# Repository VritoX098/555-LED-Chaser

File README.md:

# LED Chaser (Blinky Board)

A 10-LED chaser board built with a 555 timer and CD4017 counter. My first PCB design, made through Hack Club's Forge program.

---

---

---

---

## What it does

10 LEDs light up in sequence, one after another, creating a chasing effect. There's a potentiometer (RV1) that lets you adjust the speed of the chase, turn it one way and it goes fast, the other way and it slows down.

## How to use

1. Power it with 5V via the J1 header (2-pin socket)
2. The LEDs (D1-D10) will start chasing in sequence
3. Twist RV1 to change the blink speed

Pretty simple honestly. Plug it in and watch it go.

## Why I made this

Wanted to get into hardware and PCB design. This was the perfect beginner project to learn KiCad, understand how oscillators and counters work, and actually ship something physical. Also the batman shaped board just looks cool lol.

## What I learned

- How a 555 timer works (astable mode generates a clock pulse)
- How a CD4017 decade counter distributes that pulse across 10 outputs
- Difference between SMD and THT components
- What global labels are and why power flags exist
- How to import custom footprints (CD4017 wasn't in KiCad by default)
- PCB routing is harder than it looks (redid mine twice)

---

# Bill of Materials (BOM)

**Project:** LED Chaser (Blinky Board)  
**Total Components:** 19  
**Estimated Total Cost:** $5.09 + 33 + 7 = 45$ (Including shipping and PCB)

| Ref | Qty | Value | Footprint | Links | Unit Price | Total |
|-----|-----|-------|-----------|-------|------------|-------|
| C1 | 1 | 1 µF | Capacitor_THT:CP_Radial_D5.0mm_P2.00mm | [LCSC C43342](https://www.lcsc.com/product-detail/C43342.html) / [LCSC C1579562](https://www.lcsc.com/product-detail/C1579562.html) | $0.14 | $0.14 |
| C2 | 1 | 0.01 µF | Capacitor_THT:C_Disc_D7.5mm_W2.5mm_P5.00mm | [LCSC C454399](https://www.lcsc.com/product-detail/C454399.html) | $0.17 | $0.17 |
| D1-D10 | 10 | LED | LED_THT:LED_D3.0mm | [LCSC C264302](https://www.lcsc.com/product-detail/C264302.html) / [LCSC C99771](https://www.lcsc.com/product-detail/C99771.html) | $0.10 | $1.00 |
| J1 | 1 | Conn_01x02_Socket | PinHeader_1x02_P2.54mm_Vertical | [DigiKey 929500-01-02-RK](https://www.digikey.com/en/products/result?keywords=929500-01-02-RK) | $0.10 | $0.10 |
| J2 | 1 | Conn_01x01_Socket | PinHeader_1x01_P2.54mm_Vertical | [DigiKey PRPC001DAAN-RC](https://www.digikey.com/en/products/result?keywords=PRPC001DAAN-RC) | $0.05 | $0.05 |
| R1 | 1 | 1kΩ | R_Axial_DIN0207_L6.3mm_D2.5mm_P7.62mm_Horizontal | [DigiKey CFR-25JR-52-1K](https://www.digikey.com/en/products/detail/yageo/CFR-25JR-52-1K/11974) | $0.05 | $0.05 |
| R2 | 1 | 470Ω | R_Axial_DIN0207_L6.3mm_D2.5mm_P7.62mm_Horizontal | [DigiKey CFR-25JR-52-470R](https://www.digikey.com/en/products/detail/yageo/CFR-25JR-52-470R/11966) | $0.05 | $0.05 |
| RV1 | 1 | 50kΩ | Potentiometer_Vishay_T93YA_Vertical | [LCSC C7061697](https://www.lcsc.com/product-detail/Trimmer-Potentiometers_VISHAY-T93YA503KT20_C7061697.html) / [DigiKey 3296W-1-503LF](https://www.digikey.co.uk/en/products/detail/bourns-inc/3296W-1-503LF/1088059) | $1.58 | $1.58 |
| U1 | 1 | NE555P | DIP-8_W7.62mm | [LCSC C46749](https://www.lcsc.com/product-detail/Timers-Clocks_NE555P_C46749.html) | $0.56 | $0.56 |
| U2 | 1 | CD4017BE | N16 (DIP-16) | [LCSC C34519](https://www.lcsc.com/product-detail/Counters-Dividers_TI-CD4017BE_C34519.html) | $1.39 | $1.39 |

---

---

## Cost Breakdown

| Part | Cost |
|------|------|
| Capacitors (C1, C2) | $0.31 |
| LEDs (x10) | ~$1.00 |
| Resistors (R1, R2) | $0.10 |
| Potentiometer (RV1) | $1.58 |
| NE555P (U1) | $0.56 |
| CD4017BE (U2) | $1.39 |
| Pin Headers (J1, J2) | $0.15 |
| **PCB (JLCPCB)** | ~$2.00 (for 5 boards) |
| **Total** | **~$7.34** |

> Note: The PCB cost isn't in the component BOM above because it's separate. Total project cost ends up around $7-10 depending on shipping and where you buy. Hack Club Forge covers this, so it's basically free for me lol.

---

## Credits

Built through [Hack Club's Forge](https://forge.hackclub.com) program.

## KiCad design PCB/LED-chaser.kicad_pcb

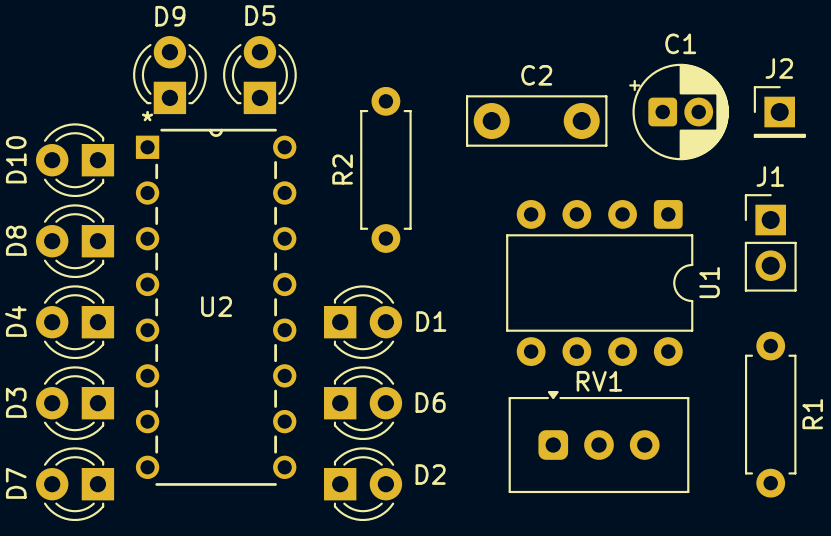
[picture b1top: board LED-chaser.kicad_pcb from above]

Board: 2 copper layers, 19 parts (0 on the bottom side), 18 nets, no tracks yet.

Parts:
C1: 1 uF; CP_Radial_D5.0mm_P2.00mm
C2: 0.01 uF; C_Disc_D7.5mm_W2.5mm_P5.00mm
D1, D2, D3, D4, D5, D6, D7, D8, D9, D10: LED; LED_D3.0mm
J1: Conn_01x02_Socket; PinHeader_1x02_P2.54mm_Vertical
J2: Conn_01x01_Socket; PinHeader_1x01_P2.54mm_Vertical
R1: 1k; R_Axial_DIN0207_L6.3mm_D2.5mm_P7.62mm_Horizontal
R2: 470; R_Axial_DIN0207_L6.3mm_D2.5mm_P7.62mm_Horizontal
RV1: 50k; Potentiometer_Vishay_T93YA_Vertical
U1: NE555P; DIP-8_W7.62mm
U2: 4017; N16

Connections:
+5V: J1.1, R1.1, U1.4 (~RST), U1.8 (VCC), U2.16 (VDD)
GND: C1.2, C2.2, J1.2, R2.2, U1.1 (GND), U2.8 (VSS), U2.13 (CKEN), U2.15 (Reset)
unnamed: D1.2 (A), U2.11 (Q9)
unnamed: D1.1 (K), D2.1 (K), D3.1 (K), D4.1 (K), D5.1 (K), D6.1 (K), D7.1 (K), D8.1 (K), D9.1 (K), D10.1 (K), R2.1
unnamed: D2.2 (A), U2.9 (Q8)
unnamed: D3.2 (A), U2.6 (Q7)
unnamed: D4.2 (A), U2.5 (Q6)
unnamed: D5.2 (A), U2.1 (Q5)
unnamed: D6.2 (A), U2.10 (Q4)
unnamed: D7.2 (A), U2.7 (Q3)
unnamed: D8.2 (A), U2.4 (Q2)
unnamed: D9.2 (A), U2.2 (Q1)
unnamed: D10.2 (A), U2.3 (Q0)
unnamed: R1.2, RV1.1
unnamed: C2.1, U1.5 (CONT)
unnamed: RV1.2, U1.7 (DISCH)
unnamed: C1.1, RV1.3, U1.2 (TRIG), U1.6 (THRES)
OUT: J2.1 (Pin_1_1), U1.3 (OUT), U2.14 (CLK)

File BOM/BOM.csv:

"Reference","Qty","Value","DNP","Exclude from BOM","Exclude from Board","Footprint","Datasheet"
"C1","1","1 uF","","","","Capacitor_THT:CP_Radial_D5.0mm_P2.00mm",""
"C2","1","0.01 uF","","","","Capacitor_THT:C_Disc_D7.5mm_W2.5mm_P5.00mm",""
"D1,D2,D3,D4,D5,D6,D7,D8,D9,D10","10","LED","","","","LED_THT:LED_D3.0mm",""
"J1","1","Conn_01x02_Socket","","","","Connector_PinHeader_2.54mm:PinHeader_1x02_P2.54mm_Vertical",""
"J2","1","Conn_01x01_Socket","","","","Connector_PinHeader_2.54mm:PinHeader_1x01_P2.54mm_Vertical",""
"R1","1","1k","","","","Resistor_THT:R_Axial_DIN0207_L6.3mm_D2.5mm_P7.62mm_Horizontal",""
"R2","1","470","","","","Resistor_THT:R_Axial_DIN0207_L6.3mm_D2.5mm_P7.62mm_Horizontal",""
"RV1","1","50k","","","","Potentiometer_THT:Potentiometer_Vishay_T93YA_Vertical",""
"U1","1","NE555P","","","","Package_DIP:DIP-8_W7.62mm","http://www.ti.com/lit/ds/symlink/ne555.pdf"
"U2","1","4017","","","","CD4017:N16","http://www.intersil.com/content/dam/Intersil/documents/cd40/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"
